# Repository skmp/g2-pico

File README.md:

### WIP schematic

### Parallel Port Pinout

pin | name (jj) | name (es) | direction | desc (es) | desc (jj)
----|----------|-----------|----------|----------|---------
1 | 5v
2 | 5v
3 | 5v
4 | 5v
5 | /MODEMCS | G2_MDMCSN | Output | Modem chip select | modem enable
6 | /IRQA | G2_IRMDMN | Input | Modem interruption | modem / lan adapter irq
7 | ??? | G2_RQDEVN | Input | Debugger /TransferRequest
8 | ??? | G2_RQEX1N | Input | External Device1 /TransferRequest
9 | ??? | G2_RQEX0N | Input | External Device0 /TransferRequest
10 | gnd
11 | gnd
12 | gnd
13 | /IRQB | G2_IREXTN | Input | External device interrupt | BBA irq
14 | /LBE or /WR | G2_BLN | output | Lowest data(G2_AD[7:0]) valid | lower byte enable or modem write
15 | ??? | G2_STN | Input | /Stop
16 | /UBE or /RD | G2_BHN | output | Highest data(G2_AD[15:8]) valid | upper byte enable or modem read
17 | 3.3v
18 | 3.3v
19 | 3.3v
20 | /BTB | G2_DSN | In/output | /DeviceSelect | input, access time / burst xfer
21 | /AEN |  G2_FRN | output | Frame signal | Address enable / bus cycle start
22 | /BTA | G2_TRN | input | /TargetReady | access time control / burst xfer
23 | gnd
24 | gnd
25-40 | AD[15:0] | G2_AD[15:0] | In/output | Address/data multiplex bus | same
41 | gnd
42 | gnd
43 | CLK | G2_CLK | output | G2bus/clock | system clock
44 | gnd
45 | gnd
46 | /RESET | G_RST | output | reset | system reset
47 | gnd
48 | gnd
49 | ??? | midi_out
50 | ??? | midi_in

### Other G2 signals
Pin | name (es) | direction | desc (es)
--|--|--|--
??? | G2_RQAICN | Input | AICA /TransferRequest
??? | G2_IRAICN | Input | AICA interruption

sources: https://web.archive.org/web/20221206012741/http://jj1odm.qp.land.to/g2bus.php, https://www.dreamcast.es/infusions/forum/viewthread.php?thread_id=21&rowstart=40, https://gamingdoc.org/technical-documentation/consoles/sega-dreamcast/independent/integrated-circuits/holly-graphics-engine/

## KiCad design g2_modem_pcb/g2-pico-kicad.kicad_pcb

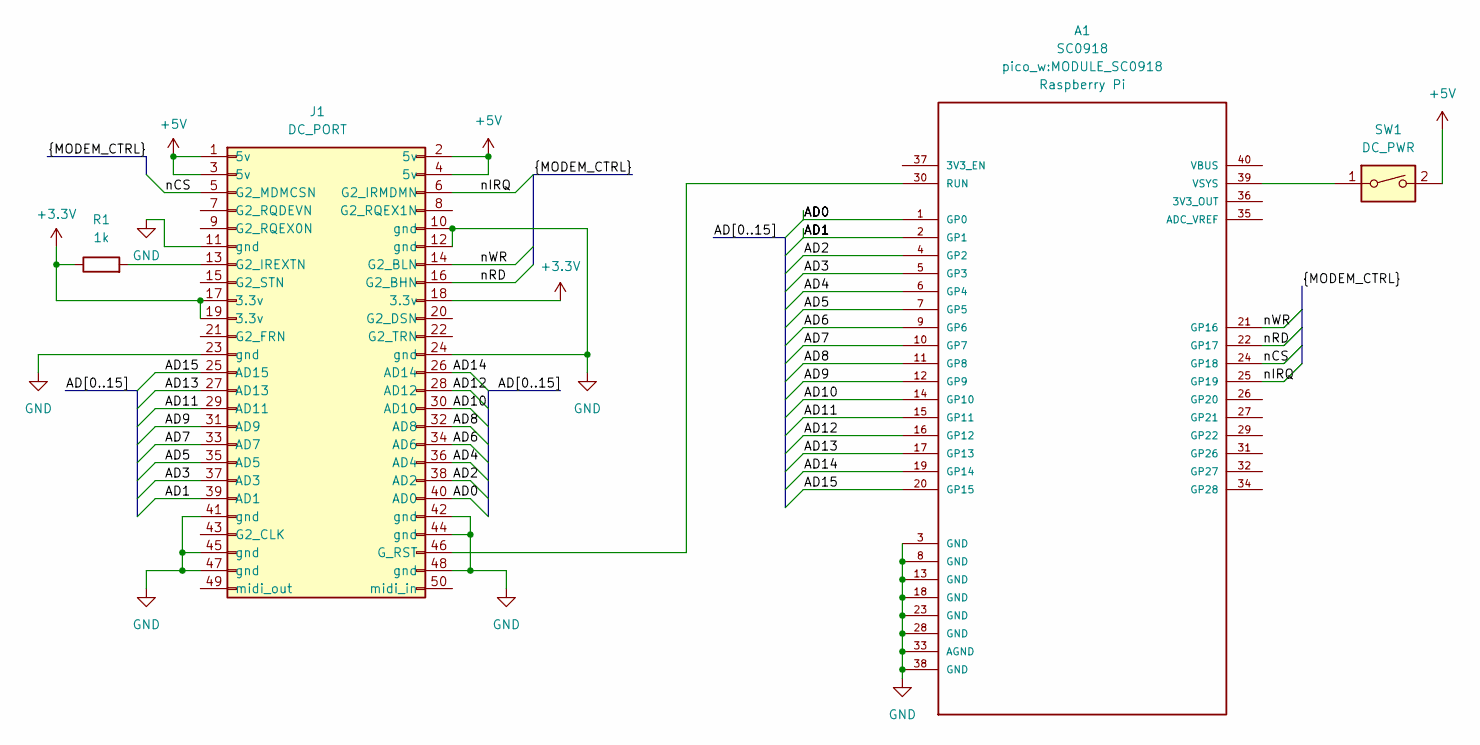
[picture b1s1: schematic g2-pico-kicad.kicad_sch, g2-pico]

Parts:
A1: SC0918; MODULE_SC0918; PARTREV 1.6
J1: DC_PORT; PinHeader_2x25_P2.00mm_Vertical_SMD
R1: 1k; R_Axial_DIN0204_L3.6mm_D1.6mm_P7.62mm_Horizontal
SW1: DC_PWR; SW_DIP_SPSTx01_Slide_9.78x4.72mm_W7.62mm_P2.54mm

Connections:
+3.3V: J1.17 (3.3v), J1.18 (3.3v), J1.19 (3.3v), R1.1
+5V: J1.1 (5v), J1.2 (5v), J1.3 (5v), J1.4 (5v), SW1.2
/AD0: A1.1 (GP0), J1.40 (AD0)
/AD1: A1.2 (GP1), J1.39 (AD1)
/AD2: A1.4 (GP2), J1.38 (AD2)
/AD3: A1.5 (GP3), J1.37 (AD3)
/AD4: A1.6 (GP4), J1.36 (AD4)
/AD5: A1.7 (GP5), J1.35 (AD5)
/AD6: A1.9 (GP6), J1.34 (AD6)
/AD7: A1.10 (GP7), J1.33 (AD7)
/AD8: A1.11 (GP8), J1.32 (AD8)
/AD9: A1.12 (GP9), J1.31 (AD9)
/AD10: A1.14 (GP10), J1.30 (AD10)
/AD11: A1.15 (GP11), J1.29 (AD11)
/AD12: A1.16 (GP12), J1.28 (AD12)
/AD13: A1.17 (GP13), J1.27 (AD13)
/AD14: A1.19 (GP14), J1.26 (AD14)
/AD15: A1.20 (GP15), J1.25 (AD15)
/nCS: A1.24 (GP18), J1.5 (G2_MDMCSN)
/nIRQ: A1.25 (GP19), J1.6 (G2_IRMDMN)
/nRD: A1.22 (GP17), J1.16 (G2_BHN)
/nWR: A1.21 (GP16), J1.14 (G2_BLN)
GND: A1.3 (GND), A1.8 (GND), A1.13 (GND), A1.18 (GND), A1.23 (GND), A1.28 (GND), A1.33 (AGND), A1.38 (GND), J1.10 (gnd), J1.11 (gnd), J1.12 (gnd), J1.23 (gnd), J1.24 (gnd), J1.41 (gnd), J1.42 (gnd), J1.44 (gnd), J1.45 (gnd), J1.47 (gnd), J1.48 (gnd)
unnamed: A1.30 (RUN), J1.46 (G_RST)
unnamed: A1.39 (VSYS), SW1.1
unnamed: J1.13 (G2_IREXTN), R1.2

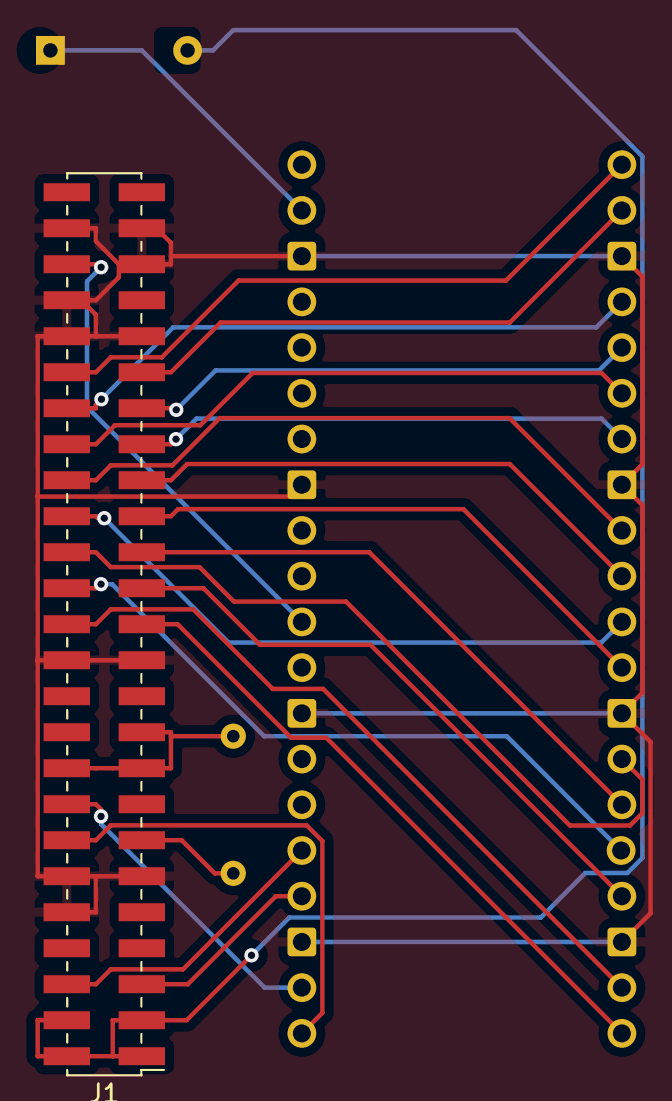
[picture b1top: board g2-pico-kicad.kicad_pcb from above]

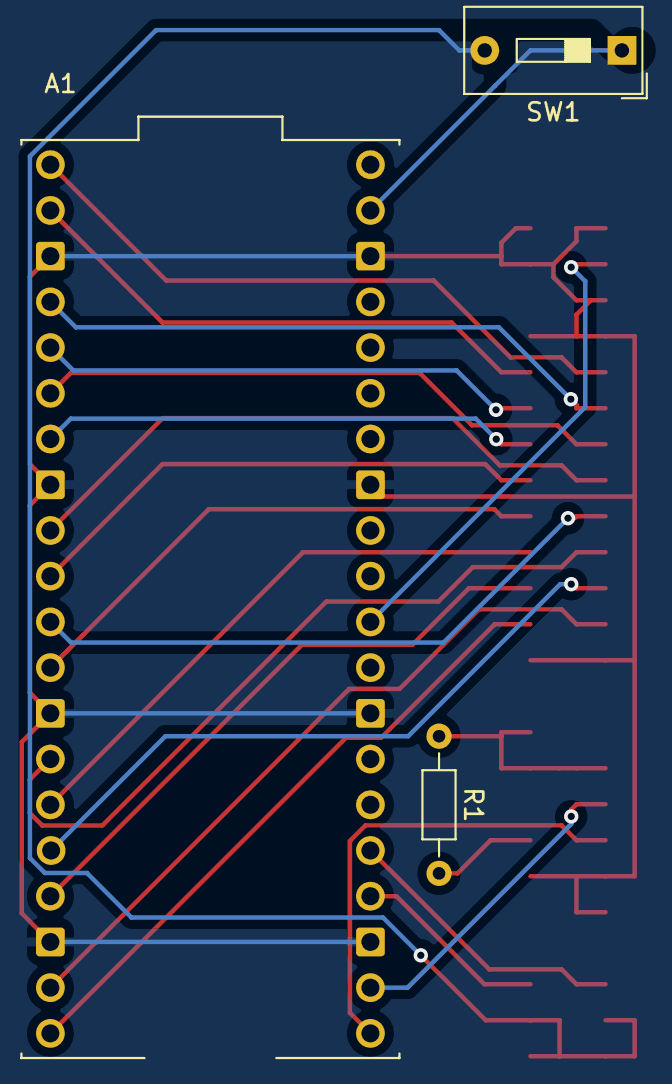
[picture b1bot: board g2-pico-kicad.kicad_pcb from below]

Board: 2 copper layers, 4 parts (3 on the bottom side), 26 nets.

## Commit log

2024-01-03 here goes nothing
2024-01-03 Fixes, add readme
2024-01-11 Add WIP schematic
2024-01-16 Add KOS example that reads/writes the g2 modem register range
